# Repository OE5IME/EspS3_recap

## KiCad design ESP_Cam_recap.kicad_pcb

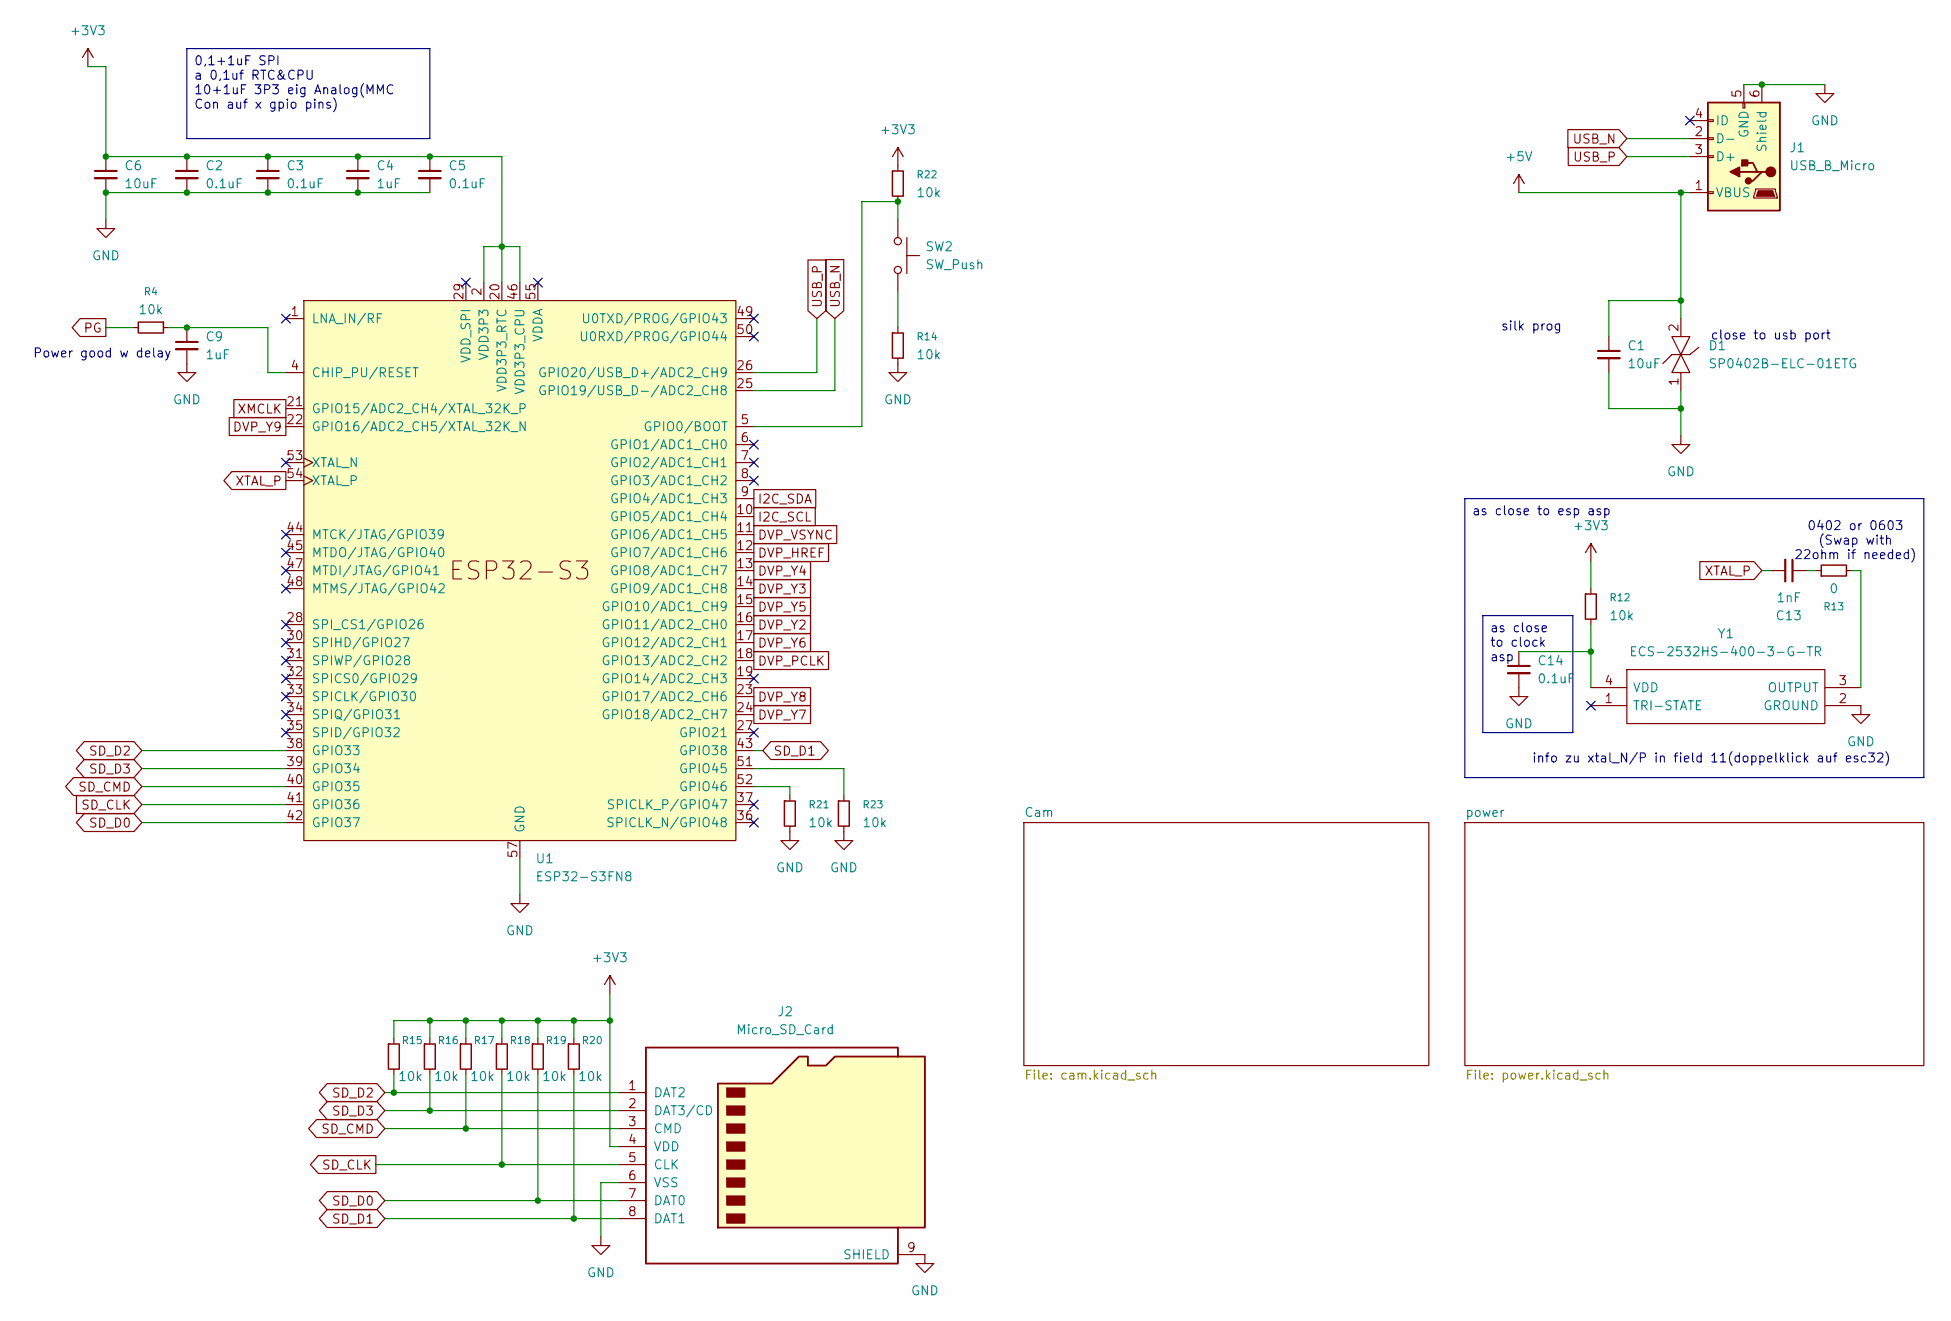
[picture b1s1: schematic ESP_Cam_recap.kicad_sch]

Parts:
C1, C6: 10uF; C_0201_0603Metric
C2, C3, C5, C14: 0.1uF; C_0201_0603Metric
C4, C9: 1uF; C_0201_0603Metric
C13: 1nF; C_0201_0603Metric
D1: SP0402B-ELC-01ETG; SP0402BELC01ETG; Mouser Part Number 576-SP0402BELC-01ETG
J1: USB_B_Micro; USB_Micro-AB_Molex_47590-0001
J2: Micro_SD_Card; microSD_HC_Molex_47219-2001
R4, R12, R14, R15, R16, R17, R18, R19, R20, R21, R22, R23: 10k; R_0201_0603Metric
R13: 0; R_0201_0603Metric
SW2: SW_Push; SW_SPST_EVQP2_ShortPushTravel_H2.5mm
U1: ESP32-S3FN8; QFN-56-1EP_7x7mm_P0.4mm_EP5.6x5.6mm
Y1: ECS-2532HS-400-3-G-TR; ECS2532HS4003GTR; Mouser Part Number 520-2532HS-400-3-G

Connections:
+3V3: C2.1, C3.1, C4.1, C5.1, C6.1, J2.4 (VDD), R12.1, R15.1, R16.1, R17.1, R18.1, R19.1, R20.1, R22.1, U1.2 (VDD3P3), U1.3 (VDD3P3), U1.20 (VDD3P3_RTC), U1.46 (VDD3P3_CPU); also elsewhere on the board
+5V: C1.1, D1.2, J1.1 (VBUS); also elsewhere on the board
-BATT: C1.2, C2.2, C3.2, C4.2, C5.2, C6.2, C9.2, C14.2, D1.1, J1.5 (GND), J1.6 (Shield), J2.6 (VSS), J2.9 (SHIELD), R14.2, R21.2, R23.2, U1.57 (GND), Y1.2 (GROUND); also elsewhere on the board
DVP_HREF: U1.12 (GPIO7/ADC1_CH6); also elsewhere on the board
DVP_PCLK: U1.18 (GPIO13/ADC2_CH2); also elsewhere on the board
DVP_VSYNC: U1.11 (GPIO6/ADC1_CH5); also elsewhere on the board
DVP_Y2: U1.16 (GPIO11/ADC2_CH0); also elsewhere on the board
DVP_Y3: U1.14 (GPIO9/ADC1_CH8); also elsewhere on the board
DVP_Y4: U1.13 (GPIO8/ADC1_CH7); also elsewhere on the board
DVP_Y5: U1.15 (GPIO10/ADC1_CH9); also elsewhere on the board
DVP_Y6: U1.17 (GPIO12/ADC2_CH1); also elsewhere on the board
DVP_Y7: U1.24 (GPIO18/ADC2_CH7); also elsewhere on the board
DVP_Y8: U1.23 (GPIO17/ADC2_CH6); also elsewhere on the board
DVP_Y9: U1.22 (GPIO16/ADC2_CH5/XTAL_32K_N); also elsewhere on the board
I2C_SCL: U1.10 (GPIO5/ADC1_CH4); also elsewhere on the board
I2C_SDA: U1.9 (GPIO4/ADC1_CH3); also elsewhere on the board
unnamed: C13.1, R13.1
unnamed: R14.1, SW2.2
unnamed: C9.1, R4.1, U1.4 (CHIP_PU/RESET)
unnamed: R22.2, SW2.1, U1.5 (GPIO0/BOOT)
unnamed: R23.1, U1.51 (GPIO45)
unnamed: R21.1, U1.52 (GPIO46)
unnamed: R13.2, Y1.3 (OUTPUT)
unnamed: C14.1, R12.2, Y1.4 (VDD)
PG: R4.2; also elsewhere on the board
SD_CLK: J2.5 (CLK), R18.2, U1.41 (GPIO36)
SD_CMD: J2.3 (CMD), R17.2, U1.40 (GPIO35)
SD_D0: J2.7 (DAT0), R19.2, U1.42 (GPIO37)
SD_D1: J2.8 (DAT1), R20.2, U1.43 (GPIO38)
SD_D2: J2.1 (DAT2), R15.2, U1.38 (GPIO33)
SD_D3: J2.2 (DAT3/CD), R16.2, U1.39 (GPIO34)
USB_N: J1.2 (D-), U1.25 (GPIO19/USB_D-/ADC2_CH8)
USB_P: J1.3 (D+), U1.26 (GPIO20/USB_D+/ADC2_CH9)
XMCLK: U1.21 (GPIO15/ADC2_CH4/XTAL_32K_P); also elsewhere on the board
XTAL_P: C13.2, U1.54 (XTAL_P)

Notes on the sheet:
Power good w delay
close to usb port
0402 or 0603 (Swap with 22ohm if needed)
silk prog
info zu xtal_N/P in field 11(doppelklick auf esc32)
as close to esp asp
0,1+1uF SPI a 0,1uf RTC&CPU 10+1uF 3P3 eig Analog(MMC Con auf x gpio pins)
as close to clock asp

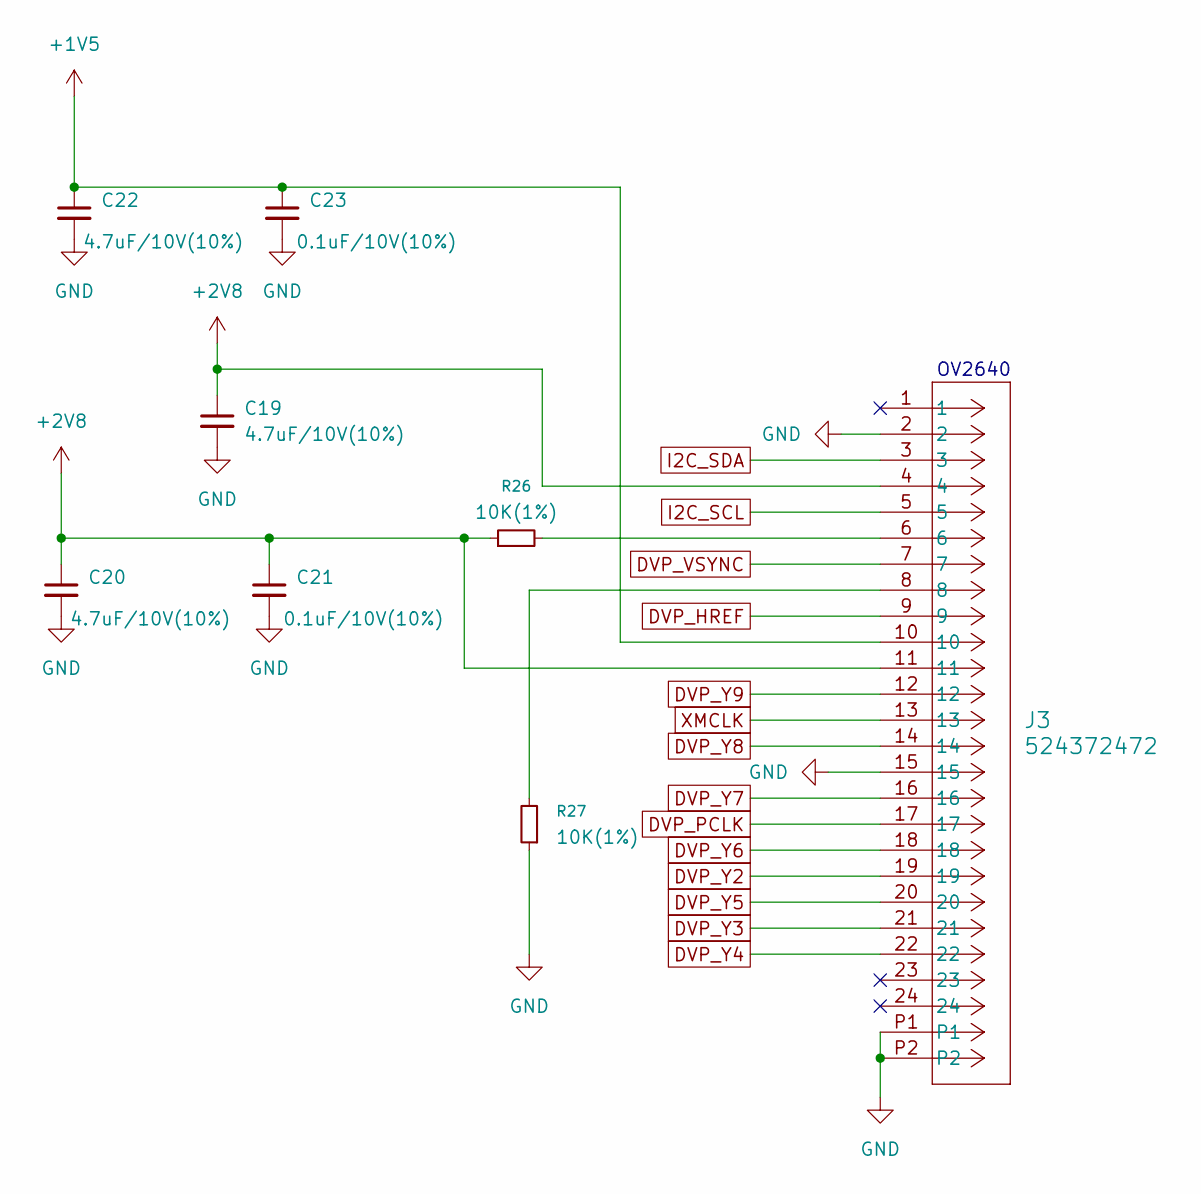
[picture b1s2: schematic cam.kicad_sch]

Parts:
C19, C20, C22: 4.7uF/10V(10%); C_0201_0603Metric
C21, C23: 0.1uF/10V(10%); C_0201_0603Metric
J3: 524372472; CON_524372472_MOL
R26, R27: 10K(1%); R_0201_0603Metric

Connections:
+1V5: C22.1, C23.1, J3.10; also elsewhere on the board
+2V8: C19.1, C20.1, C21.1, J3.4, J3.11, R26.1; also elsewhere on the board
-BATT: C19.2, C20.2, C21.2, C22.2, C23.2, J3.2, J3.15, J3.P1, J3.P2, R27.1; also elsewhere on the board
DVP_HREF: J3.9; also elsewhere on the board
DVP_PCLK: J3.17; also elsewhere on the board
DVP_VSYNC: J3.7; also elsewhere on the board
DVP_Y2: J3.19; also elsewhere on the board
DVP_Y3: J3.21; also elsewhere on the board
DVP_Y4: J3.22; also elsewhere on the board
DVP_Y5: J3.20; also elsewhere on the board
DVP_Y6: J3.18; also elsewhere on the board
DVP_Y7: J3.16; also elsewhere on the board
DVP_Y8: J3.14; also elsewhere on the board
DVP_Y9: J3.12; also elsewhere on the board
I2C_SCL: J3.5; also elsewhere on the board
I2C_SDA: J3.3; also elsewhere on the board
unnamed: J3.6, R26.2
unnamed: J3.8, R27.2
XMCLK: J3.13; also elsewhere on the board

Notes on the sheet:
OV2640

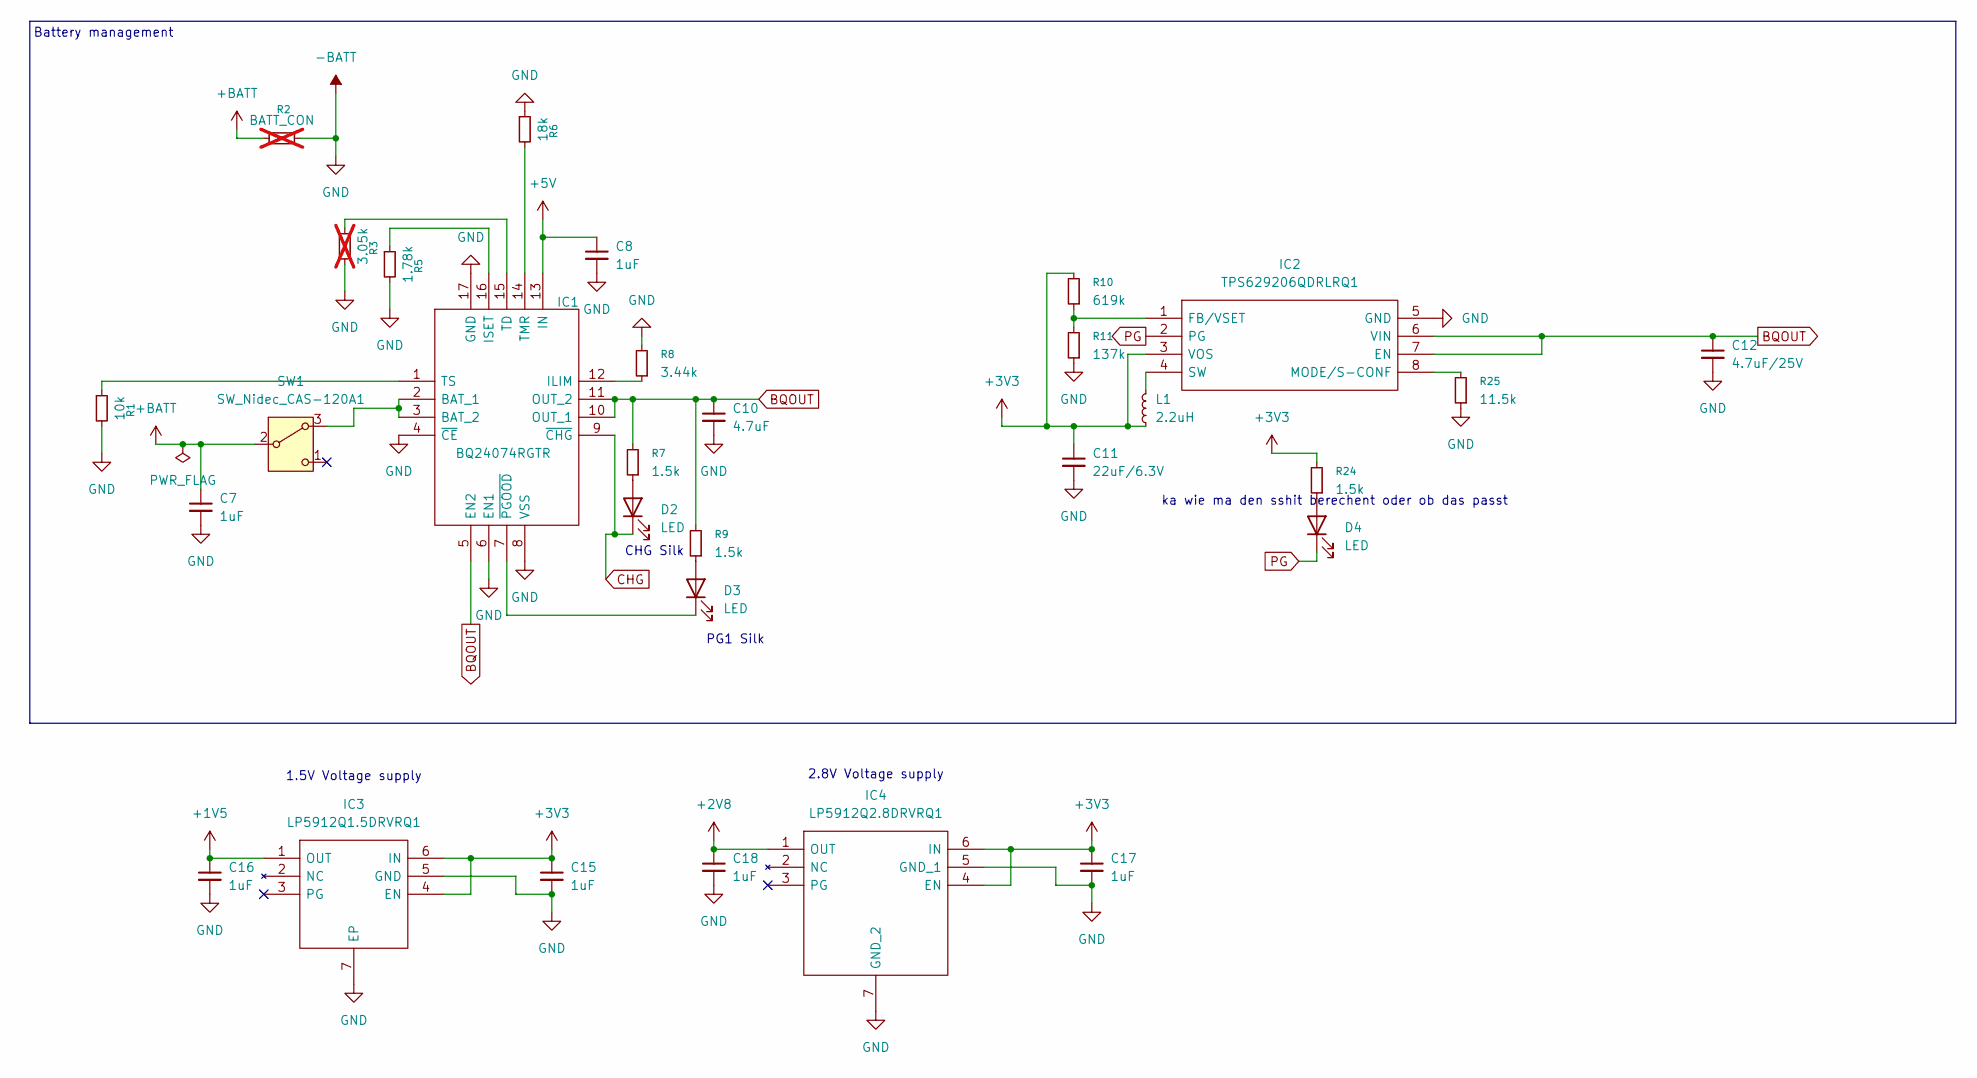
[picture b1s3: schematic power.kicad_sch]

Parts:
C7, C8, C15, C16, C17, C18: 1uF; C_0201_0603Metric
C10: 4.7uF; C_0201_0603Metric
C11: 22uF/6.3V; C_0805_2012Metric
C12: 4.7uF/25V; C_1206_3216Metric
D2, D3, D4: LED; LED_0402_1005Metric
IC1: BQ24074RGTR; QFN50P300X300X100-17N-D; Mouser Part Number 595-BQ24074RGTR
IC2: TPS629206QDRLRQ1; SOTFL50P160X60-8N; Mouser Part Number 595-TPS629206QDRLRQ1
IC3: LP5912Q1.5DRVRQ1; SON65P200X200X80-7N; Mouser Part Number 595-LP5912Q1.5DRVRQ1
IC4: LP5912Q2.8DRVRQ1; SON65P200X200X80-7N; Mouser Part Number 595-LP5912Q2.8DRVRQ1
L1: 2.2uH; L_TDK_MLZ1608
R1: 10k; R_0201_0603Metric
R2: BATT_CON; R_2512_6332Metric_Pad1.40x3.35mm_HandSolder; not fitted
R3: 3.05k; R_0201_0603Metric; not fitted
R5: 1.78k; R_0201_0603Metric
R6: 18k; R_0201_0603Metric
R7, R9, R24: 1.5k; R_0201_0603Metric
R8: 3.44k; R_0201_0603Metric
R10: 619k; R_0201_0603Metric
R11: 137k; R_0201_0603Metric
R25: 11.5k; R_0201_0603Metric
SW1: SW_Nidec_CAS-120A1; Nidec_Copal_CAS-120A

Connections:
+1V5: C16.1, IC3.1 (OUT); also elsewhere on the board
+2V8: C18.1, IC4.1 (OUT); also elsewhere on the board
+3V3: C11.1, C15.1, C17.1, IC2.3 (VOS), IC3.4 (EN), IC3.6 (IN), IC4.4 (EN), IC4.6 (IN), L1.1, R10.2, R24.2; also elsewhere on the board
+5V: C8.1, IC1.13 (IN); also elsewhere on the board
+BATT: C7.1, R2.1, SW1.2 (B)
-BATT: C7.2, C8.2, C10.2, C11.2, C12.2, C15.2, C16.2, C17.2, C18.2, IC1.4 (~CE), IC1.6 (EN1), IC1.8 (VSS), IC1.17 (GND), IC2.5 (GND), IC3.5 (GND), IC3.7 (EP), IC4.5 (GND_1), IC4.7 (GND_2), R1.2, R2.2, R3.2, R5.2, R6.1, R8.2, R11.1, R25.1; also elsewhere on the board
BQOUT: C10.1, C12.1, IC1.5 (EN2), IC1.10 (OUT_1), IC1.11 (OUT_2), IC2.6 (VIN), IC2.7 (EN), R7.2, R9.2
CHG: D2.1 (K), IC1.9 (~CHG)
unnamed: D2.2 (A), R7.1
unnamed: D3.2 (A), R9.1
unnamed: D3.1 (K), IC1.7 (~PGOOD)
unnamed: D4.2 (A), R24.1
unnamed: IC1.2 (BAT_1), IC1.3 (BAT_2), SW1.3 (A)
unnamed: IC1.12 (ILIM), R8.1
unnamed: IC1.16 (ISET), R5.1
unnamed: IC1.15 (TD), R3.1
unnamed: IC1.14 (TMR), R6.2
unnamed: IC1.1 (TS), R1.1
unnamed: IC2.1 (FB/VSET), R10.1, R11.2
unnamed: IC2.8 (MODE/S-CONF), R25.2
unnamed: IC2.4 (SW), L1.2
PG: D4.1 (K), IC2.2 (PG); also elsewhere on the board

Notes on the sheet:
Battery management
PG1 Silk
ka wie ma den sshit berechent oder ob das passt
2.8V Voltage supply
CHG Silk
1.5V Voltage supply

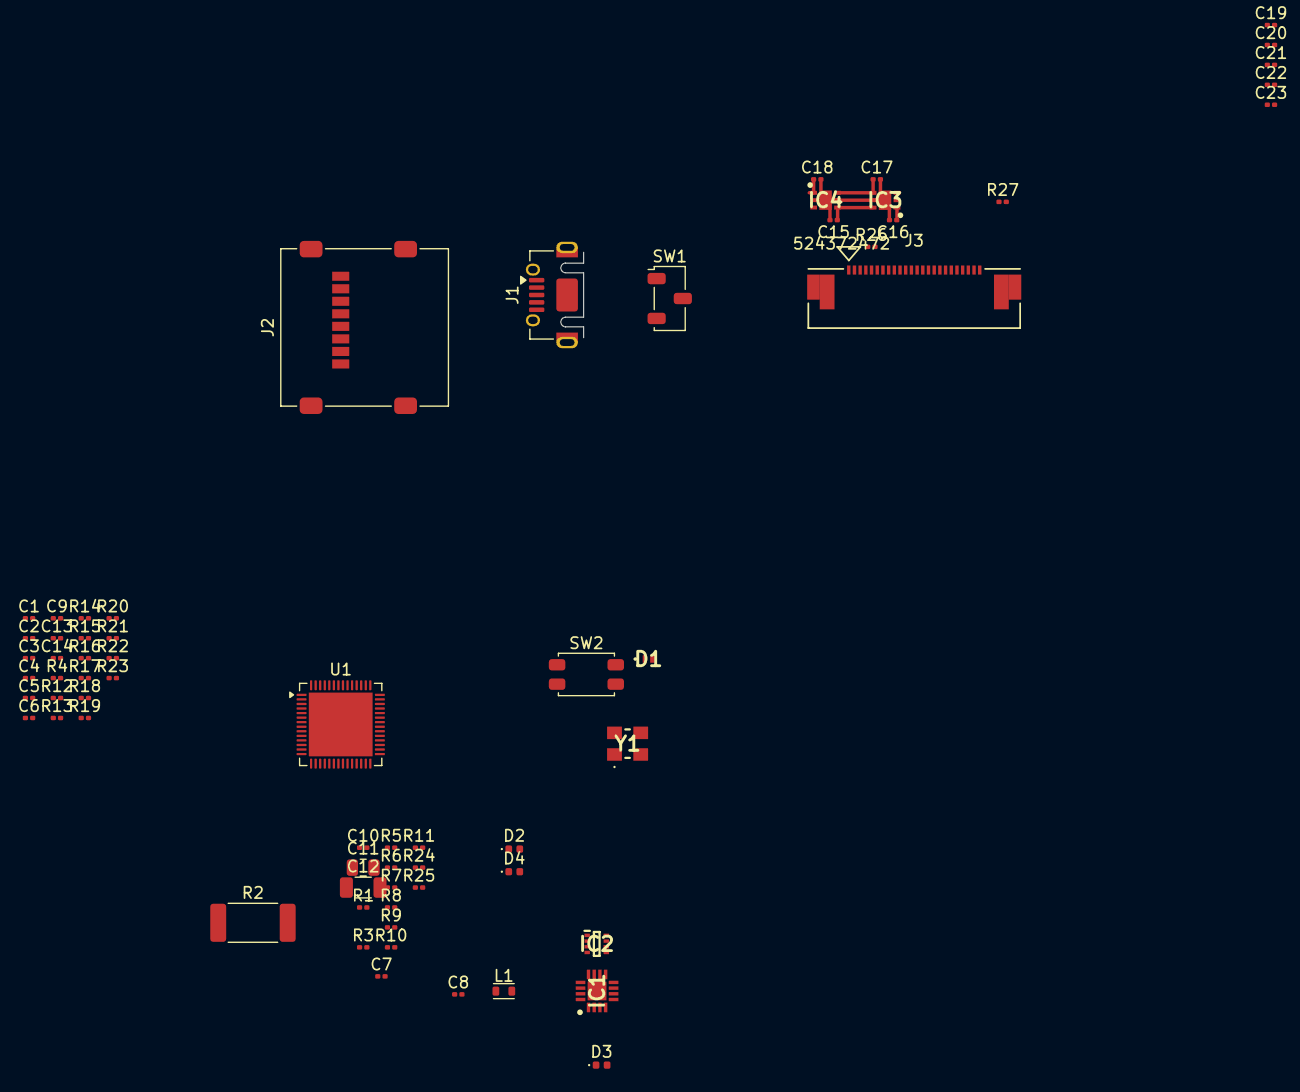
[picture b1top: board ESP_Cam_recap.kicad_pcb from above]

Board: 4 copper layers, 66 parts (0 on the bottom side), 55 nets.

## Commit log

2025-11-16 Power section
2025-11-21 power section und clock
2025-11-24 finished schematics
